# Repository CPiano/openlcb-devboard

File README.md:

# openlcb-devboard
Eagle projects for OpenLCB development boards

## Basic Directory Structure

 - **libraries**:
   Contains Eagle libraries used by one or more of the develpment boards. Libraries from
   different sources should each have their own directory under libraries.

 - **projects**:
   Contains one directory for each board. It also contains directories for templates.
   The project directory should be named according to the board it contains and the name
   should only contain lowercase letters, numbers, and hyphens. Each project directory 
   should contain the following files (where *board* matches the directory name):
   
   - ***board*.sch**: The Eagle schematic file.
   - ***board*.brd**: The Eagle PCB design file.
   - **readme.md**: Markdown file containing overview of board.
   - **spec.md**: Markdown file containing the specification for the board. This is the
     description of what the board should do and any design constraints.
   - **design-notes.md**: Any notes about why the schematic or layout was designed in a
     particular way. This is not a detailed repetition of what is in the schematic, but
     rather is a good palce to keep notes on calculations, design alternatives considered,
     links to data sheets, etc.
   - Other files needed or generated by Eagle.

   The projects directory also contains a README.md file that should be kept up to date
   with overivews of each of the project and template directories. Also note that the 
   .gitignore file for the repository is set up to ignore any of the installation specific
   and Eagle generated files. Only those files necesary to build the design are included
   in the repository.

 - **tools**: Contains Eagle rules files, scripts, etc. used as a part of developing boards.

## Notes on using Git for Eagle designs.
In general, merging schematic, board, and library files doesn't work. Git should be looked
at as a history of revisions but not as a way to manage multiple branches of the same design.
Use the following rules of thumb:

1. Each subdirectory of **projects** should have an "owner" who should control edits to the
   schematic and pcb files. Ultimately the owner of the board should make changes to these
   files and others should provide feedback outside of Eagle. It is advisable that comments
   on schematics be entered as issues on Github so that the conversation is captured and not
   lost to the abyss that is email.  

2. Markdown files can be merged by Git, so they can be changed through a normal fork and pull
   request mechanism.

3. Anyone can start a new project by forking the repository, adding a subdirectory of 
   **projects** and creating a new board. This board can then be submitted back to the main
   repository through pull request.

4. Libraries also cannot be merged reliably. There is no problem with adding new libraries,
   but they shouldn't be deleted. Caution should be used when updating the version of libraries
   to be sure that the change is backward compatible.  

## LICENSE
This work is licensed under the Creative Commons Attribution-ShareAlike 4.0
International License. To view a copy of this license, visit 
http://creativecommons.org/licenses/by-sa/4.0/ or send a letter to Creative Commons,
PO Box 1866, Mountain View, CA 94042, USA.

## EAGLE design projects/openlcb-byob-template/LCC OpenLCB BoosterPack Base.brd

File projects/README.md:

# Projects Overview

## Project Directories

- **boosterpack-can-iso**: Isolated USB to CAN adaptor BoosterPack for TI Launchpads.
- **bosterpack-io**: OpenLCC Input/Output BoosterPack for TI Launchpads.

## Template Directories

- **byob-template**: Provided by TI as a starter template for BoosterPacks. There is also a small library provided by TI in the library directory that contains a couple useful things.
- **openlcb-byob-template**:

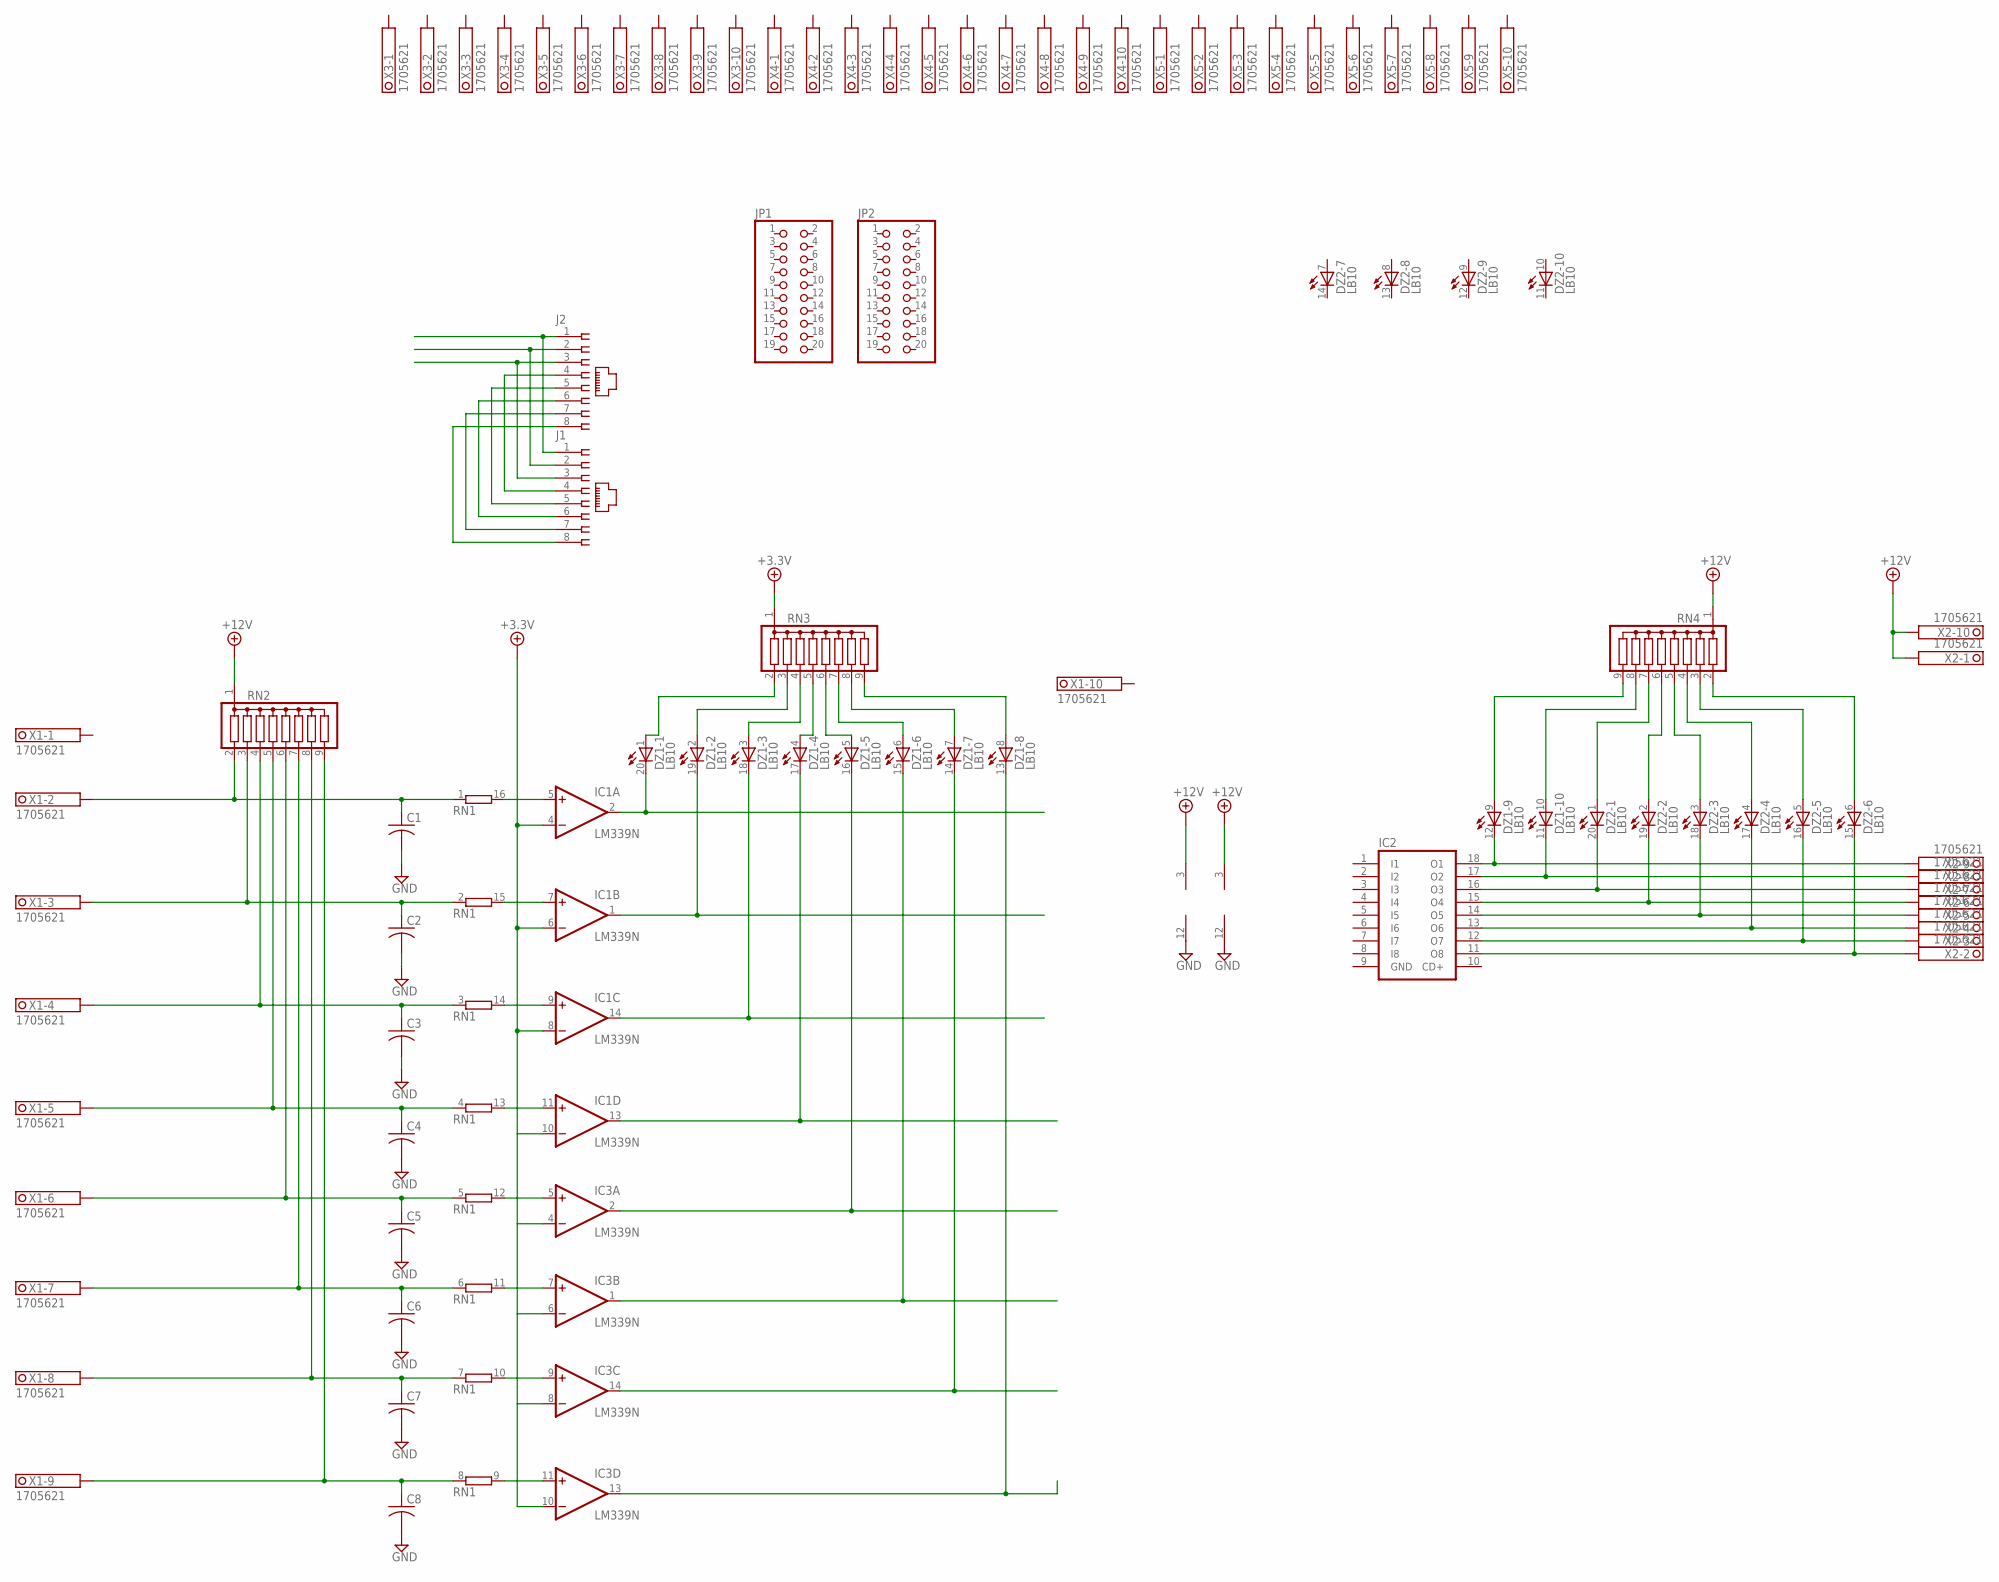
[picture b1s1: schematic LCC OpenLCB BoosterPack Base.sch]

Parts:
C1, C2, C3, C4, C5, C6, C7, C8: C-US075-032X103; C075-032X103
DZ1, DZ2: LB10
IC1, IC3: LM339N; DIL14
IC2: ULN2803A; DIL18
J1, J2: 555164-1
JP1, JP2: PINHD-2X10; 2X10
RN1: 8R-P; DIL16
RN2, RN3, RN4: G08R; SIL9
X1, X2, X3, X4, X5: 1705621

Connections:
+3.3V: IC1.4 (-IN), IC1.6 (-IN), IC1.8 (-IN), IC1.10 (-IN), IC3.4 (-IN), IC3.6 (-IN), IC3.8 (-IN), IC3.10 (-IN), RN3.1
+12V: IC1.3 (V+), IC3.3 (V+), RN2.1, RN4.1, X2.1.1, X2.1.2, X2.10.1, X2.10.2
GND: C1.2, C2.2, C3.2, C4.2, C5.2, C6.2, C7.2, C8.2, IC1.12 (GND), IC2.9 (GND), IC3.12 (GND)
unnamed: J1.1, J2.1
unnamed: J1.2, J2.2
unnamed: J1.3, J2.3
unnamed: J1.4, J2.4
unnamed: J1.5, J2.5
unnamed: J1.6, J2.6
unnamed: J1.7, J2.7
unnamed: J1.8, J2.8
unnamed: IC1.5 (+IN), RN1.16 (2)
unnamed: IC1.7 (+IN), RN1.15 (2)
unnamed: IC1.9 (+IN), RN1.14 (2)
unnamed: IC1.11 (+IN), RN1.13 (2)
unnamed: DZ1.1 (A), RN3.2
unnamed: DZ1.2 (A), RN3.3
unnamed: DZ1.3 (A), RN3.4
unnamed: DZ1.4 (A), RN3.5
unnamed: DZ1.5 (A), RN3.6
unnamed: DZ1.6 (A), RN3.7
unnamed: DZ1.7 (A), RN3.8
unnamed: DZ1.8 (A), RN3.9
unnamed: DZ1.20 (C), IC1.2 (OUT)
unnamed: DZ1.19 (C), IC1.1 (OUT)
unnamed: DZ1.18 (C), IC1.14 (OUT)
unnamed: DZ1.17 (C), IC1.13 (OUT)
unnamed: C1.1, RN1.1, RN2.2, X1.2.1, X1.2.2
unnamed: C2.1, RN1.2 (1), RN2.3, X1.3.1, X1.3.2
unnamed: C3.1, RN1.3 (1), RN2.4, X1.4.1, X1.4.2
unnamed: C4.1, RN1.4 (1), RN2.5, X1.5.1, X1.5.2
unnamed: IC3.5 (+IN), RN1.12 (2)
unnamed: IC3.7 (+IN), RN1.11 (2)
unnamed: IC3.9 (+IN), RN1.10 (2)
unnamed: IC3.11 (+IN), RN1.9 (2)
unnamed: C5.1, RN1.5 (1), RN2.6, X1.6.1, X1.6.2
unnamed: C6.1, RN1.6 (1), RN2.7, X1.7.1, X1.7.2
unnamed: C7.1, RN1.7 (1), RN2.8, X1.8.1, X1.8.2
unnamed: C8.1, RN1.8 (1), RN2.9, X1.9.1, X1.9.2
unnamed: DZ1.16 (C), IC3.2 (OUT)
unnamed: DZ1.15 (C), IC3.1 (OUT)
unnamed: DZ1.14 (C), IC3.14 (OUT)
unnamed: DZ1.13 (C), IC3.13 (OUT)
unnamed: DZ1.12 (C), IC2.18 (O1), X2.9.1, X2.9.2
unnamed: DZ1.9 (A), RN4.9
unnamed: DZ1.10 (A), RN4.8
unnamed: DZ2.1 (A), RN4.7
unnamed: DZ2.2 (A), RN4.6
unnamed: DZ2.3 (A), RN4.5
unnamed: DZ2.4 (A), RN4.4
unnamed: DZ2.5 (A), RN4.3
unnamed: DZ2.6 (A), RN4.2
unnamed: DZ1.11 (C), IC2.17 (O2), X2.8.1, X2.8.2
unnamed: DZ2.20 (C), IC2.16 (O3), X2.7.1, X2.7.2
unnamed: DZ2.19 (C), IC2.15 (O4), X2.6.1, X2.6.2
unnamed: DZ2.18 (C), IC2.14 (O5), X2.5.1, X2.5.2
unnamed: DZ2.17 (C), IC2.13 (O6), X2.4.1, X2.4.2
unnamed: DZ2.16 (C), IC2.12 (O7), X2.3.1, X2.3.2
unnamed: DZ2.15 (C), IC2.11 (O8), X2.2.1, X2.2.2

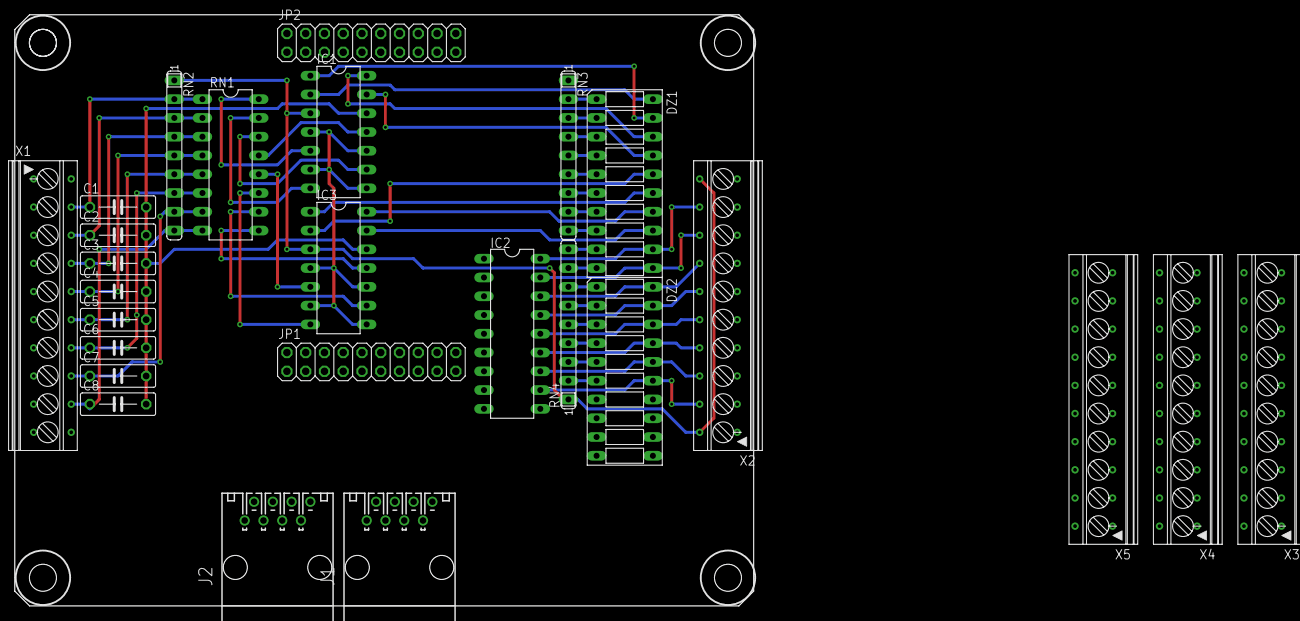
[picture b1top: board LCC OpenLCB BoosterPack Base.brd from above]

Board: 2 copper layers, 100.0 x 80.0 mm, 26 parts (0 on the bottom side), 59 nets.

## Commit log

2016-08-22 Initial repository setup
2016-08-24 Added markdown documentation files.
2016-08-24 Fixed Markdown formatting error
